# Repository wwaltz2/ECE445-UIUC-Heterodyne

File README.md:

# ECE445-UIUC-Heterodyne
For ease of sharing files, journals, code, and schematics while we design, revise, build, and report on our senior design project.

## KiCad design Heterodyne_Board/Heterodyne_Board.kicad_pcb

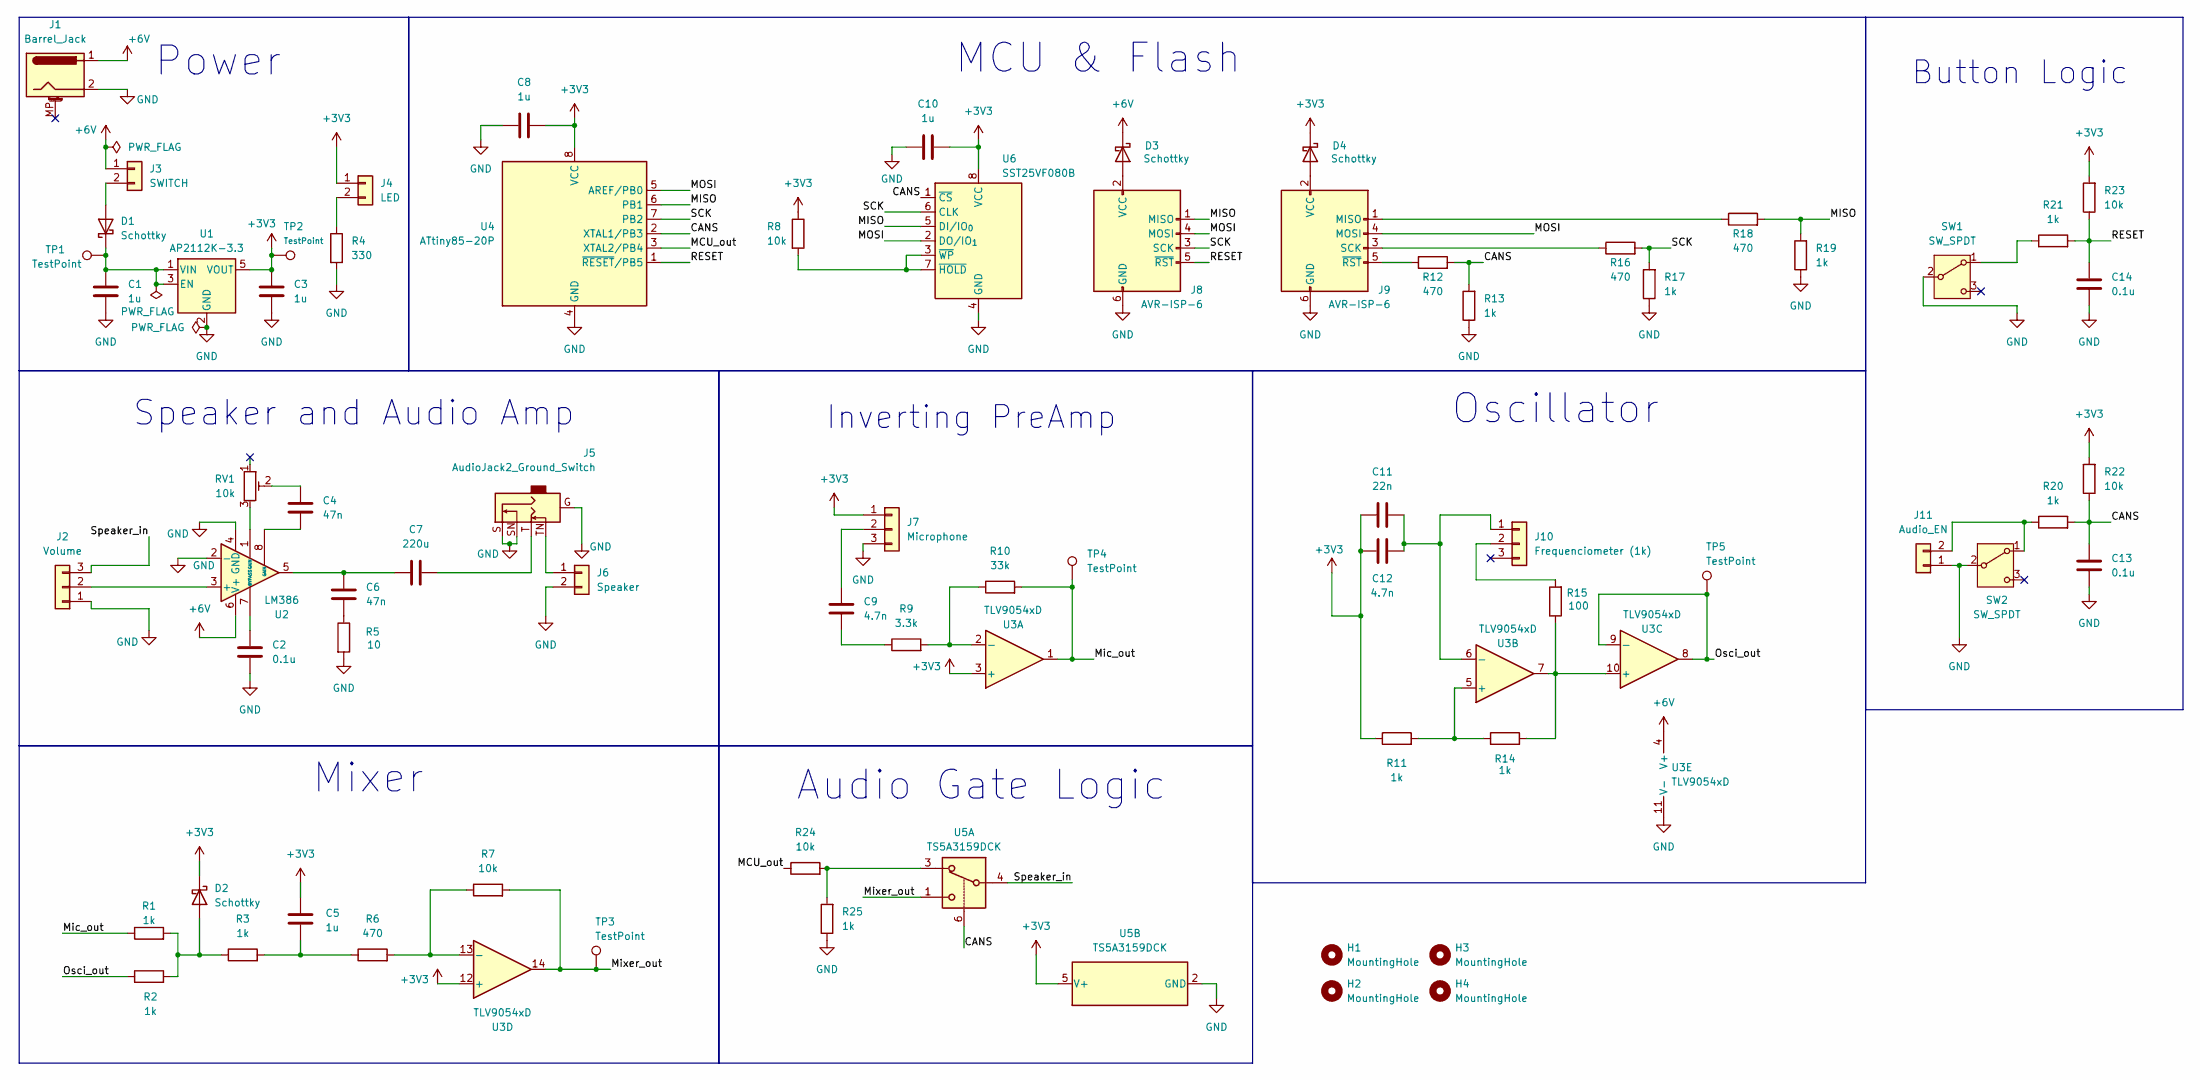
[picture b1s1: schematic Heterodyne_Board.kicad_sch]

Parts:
C1, C3, C5, C8, C10: 1u; C_0805_2012Metric_Pad1.18x1.45mm_HandSolder
C2, C13, C14: 0.1u; C_0805_2012Metric_Pad1.18x1.45mm_HandSolder
C4, C6: 47n; C_0805_2012Metric_Pad1.18x1.45mm_HandSolder
C7: 220u; C_Radial_D6.3mm_H11.0mm_P2.50mm
C9, C12: 4.7n; C_0805_2012Metric_Pad1.18x1.45mm_HandSolder
C11: 22n; C_0805_2012Metric_Pad1.18x1.45mm_HandSolder
D1, D2, D3, D4: Schottky; D_SOD-123
H1, H2, H3, H4: MountingHole; MountingHole_3.2mm_M3
J1: Barrel_Jack; BarrelJack_Horizontal
J2: Volume; Molex_KK-254_AE-6410-03A_1x03_P2.54mm_Vertical
J3: SWITCH; Molex_KK-254_AE-6410-02A_1x02_P2.54mm_Vertical
J4: LED; Molex_KK-254_AE-6410-02A_1x02_P2.54mm_Vertical
J5: AudioJack2_Ground_Switch; Jack_3.5mm_CUI_SJ1-3525N_Horizontal
J6: Speaker; Molex_KK-254_AE-6410-02A_1x02_P2.54mm_Vertical
J7: Microphone; Molex_KK-254_AE-6410-03A_1x03_P2.54mm_Vertical
J8: AVR-ISP-6; IDC-Header_2x03_P2.54mm_Vertical
J9: AVR-ISP-6; PinHeader_2x03_P2.54mm_Vertical
J10: Frequenciometer (1k); Molex_KK-254_AE-6410-03A_1x03_P2.54mm_Vertical
J11: Audio_EN; Molex_KK-254_AE-6410-02A_1x02_P2.54mm_Vertical
R1, R2, R3, R11, R13, R14, R17, R19, R20, R21, R25: 1k; R_0805_2012Metric_Pad1.20x1.40mm_HandSolder
R4: 330; R_0805_2012Metric_Pad1.20x1.40mm_HandSolder
R5: 10; R_0805_2012Metric_Pad1.20x1.40mm_HandSolder
R6, R12, R16, R18: 470; R_0805_2012Metric_Pad1.20x1.40mm_HandSolder
R7, R8, R22, R23, R24: 10k; R_0805_2012Metric_Pad1.20x1.40mm_HandSolder
R9: 3.3k; R_0805_2012Metric_Pad1.20x1.40mm_HandSolder
R10: 33k; R_0805_2012Metric_Pad1.20x1.40mm_HandSolder
R15: 100; R_0805_2012Metric_Pad1.20x1.40mm_HandSolder
RV1: 10k; Potentiometer_Bourns_TC33X_Vertical
SW1, SW2: SW_SPDT; SW_Slide_SPDT_Straight_CK_OS102011MS2Q
TP1, TP2, TP3, TP4, TP5: TestPoint; TestPoint_Pad_1.0x1.0mm
U1: AP2112K-3.3; SOT-23-5
U2: LM386; DIP-8_W7.62mm
U3: TLV9054xD; SOIC-14_3.9x8.7mm_P1.27mm
U4: ATtiny85-20P; DIP-8_W7.62mm
U5: TS5A3159DCK; SOT-363_SC-70-6
U6: SST25VF080B; DIP-8_W7.62mm

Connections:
+3V3: C3.1, C5.1, C8.2, C10.2, C11.1, C12.1, D2.1 (K), D4.1 (K), J4.1, J7.1, R8.1, R11.1, R22.2, R23.2, TP2.1, U1.5 (VOUT), U3.3 (+), U3.12 (+), U4.8 (VCC), U5.5 (V+), U6.8 (VCC)
+6V: D3.1 (K), J1.1, J3.1, U2.6 (V+), U3.4 (V+)
/CANS: C13.2, R12.2, R13.2, R20.2, R22.1, U4.2 (XTAL1/PB3), U5.6, U6.1 (~CS)
/MCU_out: R24.1, U4.3 (XTAL2/PB4)
/MISO: J8.1 (MISO), R18.2, R19.2, U4.6 (PB1), U6.5 (DI/IO_{0})
/MOSI: J8.4 (MOSI), J9.4 (MOSI), U4.5 (AREF/PB0), U6.2 (DO/IO_{1})
/Mic_out: R1.1, R10.2, TP4.1, U3.1
/Mixer_out: R7.2, TP3.1, U3.14, U5.1
/Osci_out: R2.1, TP5.1, U3.8, U3.9 (-)
/RESET: C14.2, J8.5 (~RST), R21.2, R23.1, U4.1 (~RESET/PB5)
/SCK: J8.3 (SCK), R16.2, R17.2, U4.7 (PB2), U6.6 (CLK)
/Speaker_in: J2.3, U5.4
GND: C1.2, C2.1, C3.2, C8.1, C10.1, C13.1, C14.1, J1.2, J2.1, J5.G, J5.S, J5.SN, J6.2, J7.3, J8.6 (GND), J9.6 (GND), J11.1, R4.2, R5.2, R13.1, R17.1, R19.1, R25.1, SW1.2 (B), SW2.2 (B), U1.2 (GND), U2.2 (-), U2.4 (GND), U3.11 (V-), U4.4 (GND), U5.2 (GND), U6.4 (GND)
unnamed: C4.1, U2.8 (GAIN)
unnamed: C4.2, RV1.2
unnamed: C5.2, R3.2, R6.1
unnamed: C6.1, R5.1
unnamed: C6.2, C7.1, U2.5
unnamed: C7.2, J5.T
unnamed: C9.2, R9.1
unnamed: D1.2 (A), J3.2
unnamed: C1.1, D1.1 (K), TP1.1, U1.1 (VIN), U1.3 (EN)
unnamed: D2.2 (A), R1.2, R2.2, R3.1
unnamed: D3.2 (A), J8.2 (VCC)
unnamed: D4.2 (A), J9.2 (VCC)
unnamed: J2.2, U2.3 (+)
unnamed: J4.2, R4.1
unnamed: J5.TN, J6.1
unnamed: C9.1, J7.2
unnamed: J9.1 (MISO), R18.1
unnamed: J9.3 (SCK), R16.1
unnamed: J9.5 (~RST), R12.1
unnamed: C11.2, C12.2, J10.1, U3.6 (-)
unnamed: J10.2, R15.2
unnamed: J11.2, R20.1, SW2.1 (A)
unnamed: R24.2, R25.2, U5.3
unnamed: RV1.3, U2.1 (GAIN)
unnamed: R21.1, SW1.1 (A)
unnamed: C2.2, U2.7 (BYPASS)
unnamed: R9.2, R10.1, U3.2 (-)
unnamed: R11.2, R14.1, U3.5 (+)
unnamed: R14.2, R15.1, U3.7, U3.10 (+)
unnamed: R6.2, R7.1, U3.13 (-)
unnamed: R8.2, U6.3 (~WP), U6.7 (~HOLD)

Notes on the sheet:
MCU & Flash
Inverting PreAmp
Speaker and Audio Amp
Oscillator
Power
Mixer
Button Logic
Audio Gate Logic

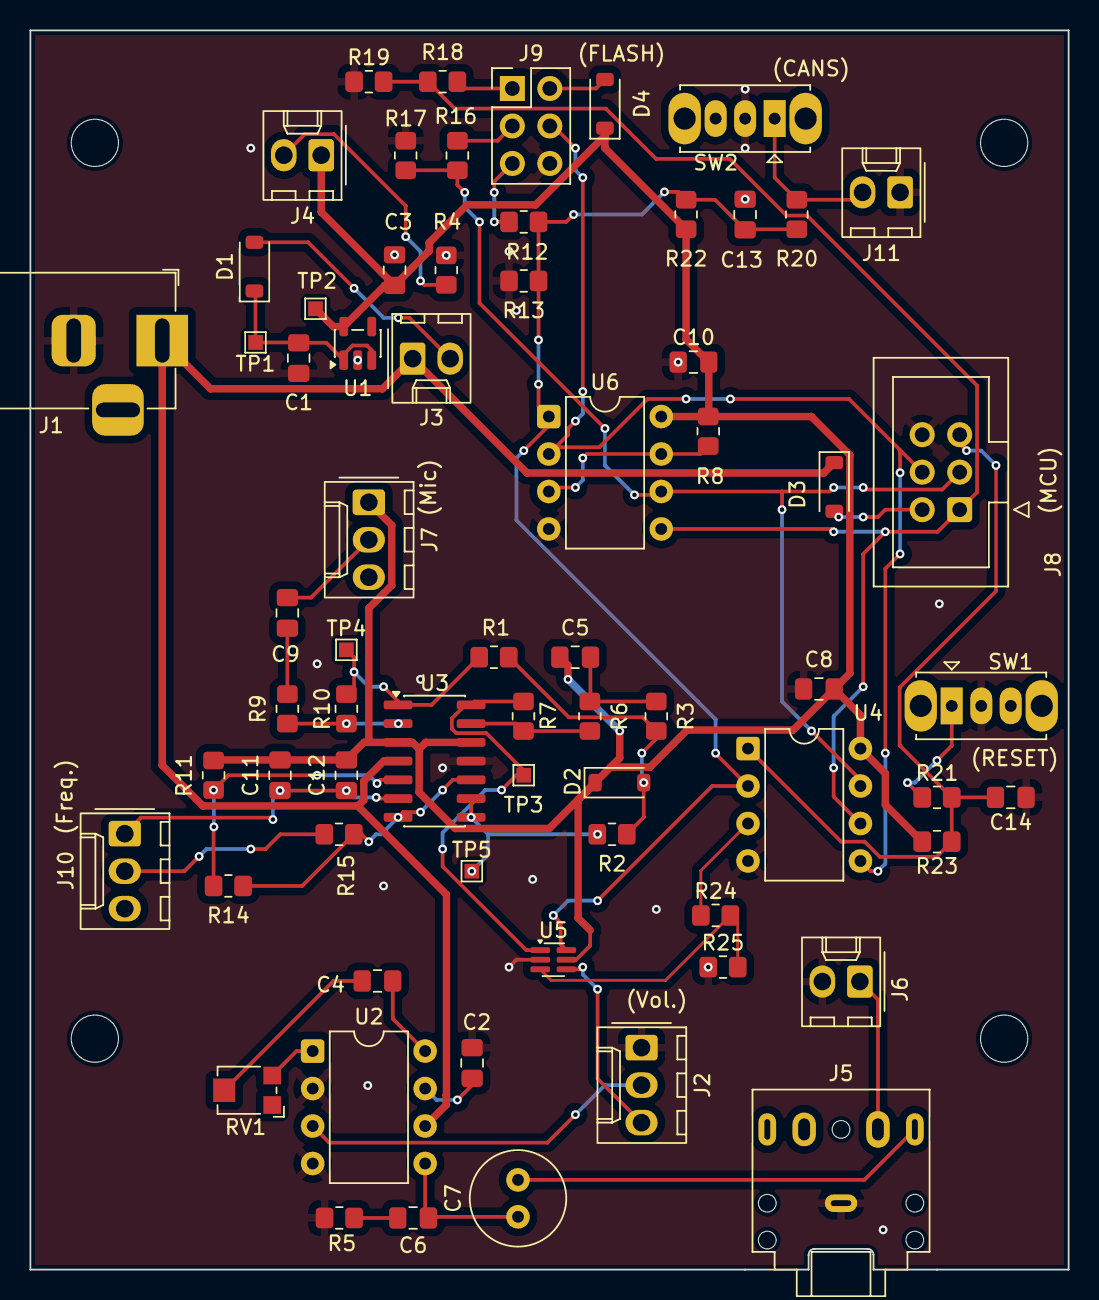
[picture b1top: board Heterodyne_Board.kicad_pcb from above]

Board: 2 copper layers, 70.4 x 84.0 mm, 72 parts (0 on the bottom side), 44 nets.

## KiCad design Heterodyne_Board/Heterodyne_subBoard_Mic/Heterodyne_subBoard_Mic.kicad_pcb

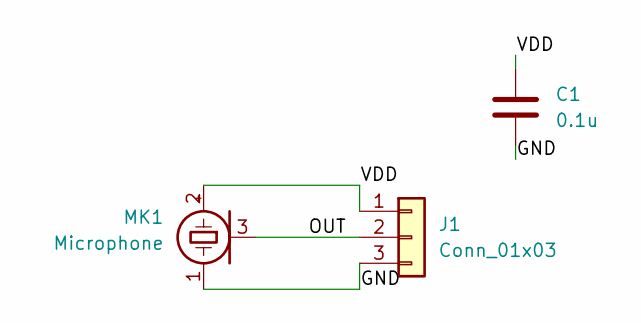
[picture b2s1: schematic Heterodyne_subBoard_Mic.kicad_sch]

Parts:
C1: 0.1u; C_0805_2012Metric_Pad1.18x1.45mm_HandSolder
J1: Conn_01x03; PinHeader_1x03_P2.54mm_Vertical
MK1: Microphone; 445_MEMS-5_3.5x2.65mm

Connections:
/GND: C1.2, J1.3, MK1.1 (-)
/OUT: J1.2, MK1.3 (+)
/VDD: C1.1, J1.1, MK1.2 (+)

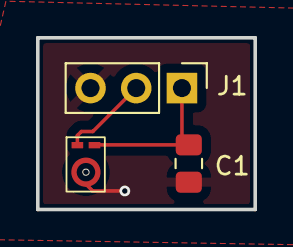
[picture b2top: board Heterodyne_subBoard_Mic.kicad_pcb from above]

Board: 2 copper layers, 12.1 x 9.5 mm, 3 parts (0 on the bottom side), 3 nets.

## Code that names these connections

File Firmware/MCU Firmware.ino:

//Sketch for MCU-Flash Audio Player
//Cycling through 5 on-board audio files
//new file on each button press

// #define MOSI PIN_PB0
// #define MISO PIN_PB1
// #define SCK PIN_PB2
// #define RST PIN_PB5

// might be unneccessary ^^^^^^^^^^^^^^^^^^^^^^^^^^^^^

#include <Adafruit_TinyFlash.h>

#define AUDIO_EN PIN_PB3
#define MCU_OUT PIN_PB4

// #if(F_CPU == 16000000L) // from Adafruit_TinyFlash TrinketPlayer.ino - this is for 8MHz, we want 16MHz?
// #error "Clock Speed Error" // what is the clock speed of our MCU?
// #endif

// /////////////////////////////////////
Adafruit_TinyFlash flash; // from Adafruit_TinyFlash TrinketPlayer.ino
uint16_t           sample_rate, delay_count;
uint32_t           samples;
volatile uint32_t  index = 0L;
// /////////////////////////////////////

uint8_t audio_index;
uint8_t file[4] = {0, 0x020000, 0x040000, 0x060000};

void setup() {
    uint8_t data[6];
    uint32_t bytes;

    if(!(bytes = flash.begin())) {
        //some sort of error message
    }
    
    flash.beginRead(0);
    for(uint8_t i=0; i<6; i++) data[i] = flash.readNextByte(); // bytes 0-1 = sample rate
                                                               // bytes 2-5 = number of samples // how does this apply to several different samples?
    sample_rate = ((uint16_t)data[0] <<  8) |  (uint16_t)data[1];
    samples     = ((uint32_t)data[2] << 24) | ((uint32_t)data[3] << 16) | ((uint32_t)data[4] <<  8) |  (uint32_t)data[5];

    //Phase Locked Loop Control and Status Register = PLLCSR
    //PLLE = Phase Locked Loop Enable
    PLLCSR |= _BV(PLLE);
    delayMicroseconds(100);
    while(!(PLLCSR & _BV(PLOCK))); // PLOCK = ????
    PLLCSR |= _BV(PCKE);

    //setting up timer for PWM output
    TIMSK  = 0;
    TCCR1  = _BV(CS10); 
    GTCCR  = _BV(PWM1B) | _BV(COM1B1);
    OCR1C  = 255;
    OCR1B  = 127;

    pinMode(AUDIO_EN, INPUT); //necessary?
    // enable internal pullup
    digitalWrite(AUDIO_EN, HIGH);
    pinMode(MCU_OUT, OUTPUT); //make sure pin PB4 is pin 4?

    audio_index = 0;
}

void loop() {


    if (digitalRead(AUDIO_EN)==LOW){
        digitalWrite(AUDIO_EN, LOW); // is this terrible form

        //do sound play
        flash.beginRead(file[audio_index]+6);
        

        digitalWrite(AUDIO_EN, HIGH);
        audio_index++;
        audio_index = audio_index % 4; // or however many files we got
    } else {
        digitalWrite(AUDIO_EN, HIGH);
    }

}

ISR(TIMER0_COMPA_vect){
    OCR1B = flash.readNextByte();
    if(++index >= samples) {
        index = 0;
        flash.endRead();
        flash.beginRead(6);
    }
}

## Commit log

2026-01-23 added folders and my first journal entry :)
2026-01-24 Create idk
2026-01-24 Added Jan23 log
2026-01-24 lol
    changed one word
2026-01-28 Create evandm2 Engineering Log 1-27-26
2026-01-28 Create evandm2 Engineering Log 1-27-26.md
    made it markdown
2026-01-28 Update evandm2 Engineering Log 1-27-26.md
    will update l8r
2026-02-10 Create 2-10-2026
    Log 2/10/2026
2026-02-16 Kyle Log 2-16-2026
2026-02-16 Rename evandm2 Engineering Log 1-23-26.txt to evandm2 Engineering Log 1-23-26.md
2026-02-16 fixed folders
2026-02-16 Update evandm2 Engineering Log 1-23-26.md
    fixed formatting
2026-02-16 Create evandm2 Engineering Log 2-14-26.md
    WIP
2026-02-16 Rename image.png to block_diagram.png
2026-02-16 Update evandm2 Engineering Log 2-14-26.md
    testing image upload
2026-02-16 Update evandm2 Engineering Log 2-14-26.md
    image successful
2026-02-17 Began PCB design
2026-02-17 Added current-limiting R on LED
2026-02-17 PreAmp Completed
    Finished schematic of Microphone output preamp and journal entry pre TA meeting
2026-02-17 Finished Speaker and Audio Amp Design
    and did journal entry
2026-02-19 pushing schematic so evan can see
    lololol
2026-02-19 inverted op amp for team captain
    team captain as a role is not confirmed. we may make Evan the court jester
2026-02-19 what a greeeeaaat work
    letsa go!
2026-02-19 Update evandm2 Engineering Log 2-18-26.md
    changed date
2026-02-19 Create evandm2 Engineering Log 2-17-26.md
    posthumous log
2026-02-19 i brokje everything
    got rid of the mixer bc i made an adder instead!!!! HECK!!!! audio module fixed, oscillator still bad :((
2026-02-20 fixed osc and mixer
2026-02-20 Schematic dun dun DUN
2026-02-20 continued PCB design
    modules organized except for audio amp, no wiring yet
2026-02-20 finished the basic PCB layout
    no wiring has been done yet though
2026-02-20 added two new testpoints
2026-02-20 Create evandm2 Engineering Log 2-20-26.md
    Quick log 12 entry
2026-02-20 Added spice simulations
2026-02-21 Create 2-21-26.txt kaj
2026-02-24 schematic additions
    added audio jack + switches that were forgotten. need to get going on pcb BADLY, no log yet
2026-02-25 started routing + fixed schematic
2026-02-26 Pushin P
    done with routing!
2026-02-26 initial pcb design finished
    missing a couple things but we ship
2026-03-02 Fixed MOSI/MISO line, lab entry for 3-1
2026-03-03 added switch between mcu and mixer for audio output definition
2026-03-03 fixed routing on switch chip
2026-03-03 added subboards under motherboard file, began firmware dev, flipped switch inputs
2026-03-04 Board round 2 complete, GBRs sent
    Also removed some of the automatic backups cuz they weren't necessary. Made discrete footprint for microphone
2026-03-04 found arduino firmware for a similar project
2026-03-05 WIP CAD parts
2026-03-05 Added Program Flowchart
2026-03-06 Record design review feedback
2026-03-06 More work done on firmware
2026-03-06 added wav files
2026-03-08 fixed memory flash and made wav files
2026-03-09 Updated PCB
    Mounting holes, second ISP header, wider board. Total dimensions about 70x70mm now.
2026-03-09 pushing working audioloader
2026-03-09 pushing tinyAHHH
2026-03-10 Add notes for week of breadboard demo
2026-03-12 Round 3 PCB upload
2026-03-22 Heck yeah we got sound!
    fixed everything somehow
2026-03-23 updated schematic a lil
2026-03-23 Chassis Assembly V1
2026-03-23 attempted to fix mixer
    made progress by changing 3v3 references to GND but spice is being weird and not converging...
2026-03-24 updated board with mcu flash fixes
2026-03-24 added toggle switches for ease of programming on board
2026-03-24 finished mcu flash schematic and audio gate logic
    from now on, mcu audio will play iff the button is held down!!!
2026-03-24 FINAL BOARD REV
2026-03-24 additional attempts at fixing mixer+oscillator
    it works on breadboard now though so yay
2026-03-24 Create evandm2 Engineering Log 3-24-26.md
    start of log
2026-03-25 stared at bill pcb
    it good
2026-03-26 submitted board rev 4
    PCB sent off to fab
2026-03-27 Chassis V2
2026-04-06 second iteration of firmware and software!
    literally no errors probably
2026-04-09 Chassis V2.5 & Printer Files
2026-04-10 even more firmware fixes
    uint8 substituted for uint32 lol
2026-04-10 even more firmware updates
    duh
2026-04-14 3d printer 3mf and gcode
2026-04-14 3mf gcode
2026-04-16 kaj5 4-16-26
2026-04-19 cad work? maybe
    Lemme know kyle can open this
2026-04-19 put assembly stl in 3d printer files
2026-04-19 did more lol
2026-04-19 Finished audio engineering
2026-04-20 Chassis V3
2026-04-22 Top shell hole modifications
2026-04-22 new top shell gcode
2026-04-23 Update evandm2 Engineering Log 4-23-26.md
    couple changes to my log
2026-04-27 Rename evandm2 Engineering Log 4-27-26.md to evandm2 Engineering Log 4-26-26.md
    oops wrong date
2026-04-27 Update evandm2 Engineering Log 4-27-26.md
    quick update
2026-04-27 last minute bottom shell changes
2026-04-28 working audiotransfer, loader, and player
2026-05-03 Create evandm2 Engineering Log 5-3-26.md
    thee final log [probably }
2026-05-05 removed redundant firmware files
    happy camping guys
2026-05-06 Final journal
